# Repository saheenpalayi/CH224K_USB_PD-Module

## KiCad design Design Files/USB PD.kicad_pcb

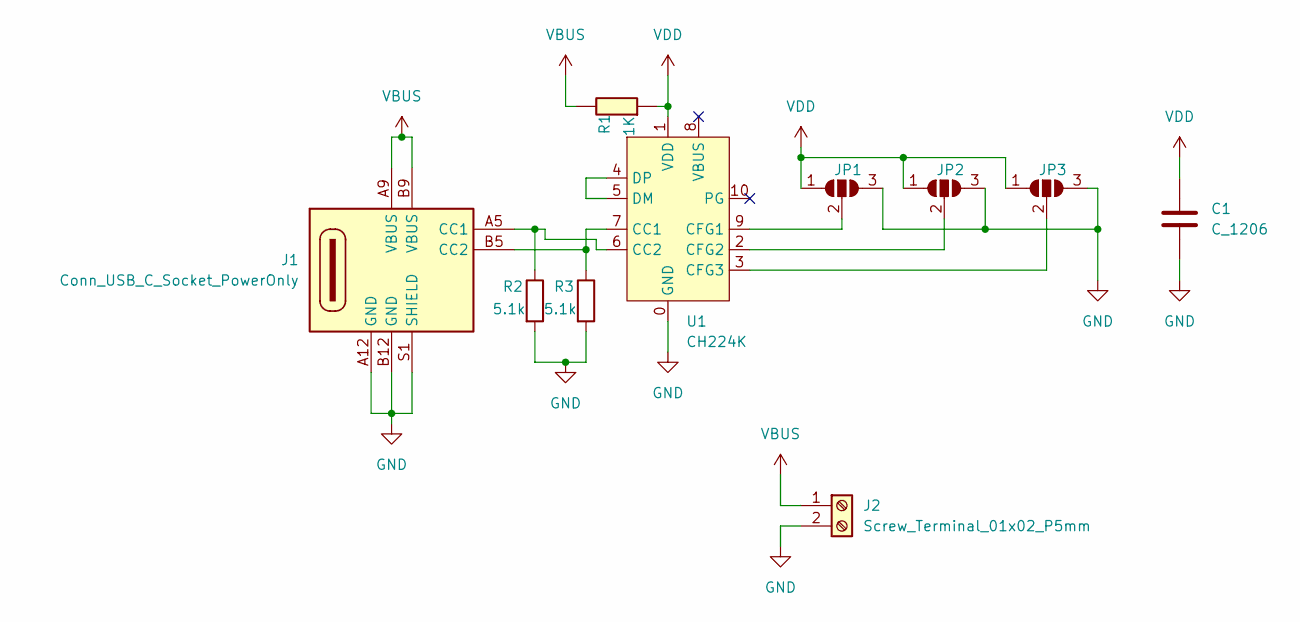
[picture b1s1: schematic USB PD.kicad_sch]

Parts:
C1: C_1206
J1: Conn_USB_C_Socket_PowerOnly; Conn_USB_C_Socket_GCT_USB4125-GF-A-0190
J2: Screw_Terminal_01x02_P5mm; TerminalBlock_OnShore_1x02_P5.00mm_Horizontal
JP1, JP2, JP3: SolderJumper_3_Open; SolderJumper-3_P1.3mm_Open_RoundedPad1.0x1.5mm
R1: 1K; R_1206
R2, R3: 5.1k; R_0805_2012Metric_Pad1.20x1.40mm_HandSolder
U1: CH224K; ESSOP-10_CH224K

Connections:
GND: C1.2, J1.A12 (GND), J1.B12 (GND), J1.S1 (SHIELD), J2.2, JP1.3 (B), JP2.3 (B), JP3.3 (B), R2.2, R3.2, U1.0 (GND)
unnamed: J1.A5 (CC1), R2.1, U1.6 (CC2)
unnamed: J1.B5 (CC2), R3.1, U1.7 (CC1)
unnamed: JP1.2 (C), U1.9 (CFG1)
unnamed: JP2.2 (C), U1.2 (CFG2)
unnamed: JP3.2 (C), U1.3 (CFG3)
unnamed: U1.4 (DP), U1.5 (DM)
VBUS: J1.A9 (VBUS), J1.B9 (VBUS), J2.1, R1.1
VDD: C1.1, JP1.1 (A), JP2.1 (A), JP3.1 (A), R1.2, U1.1 (VDD)

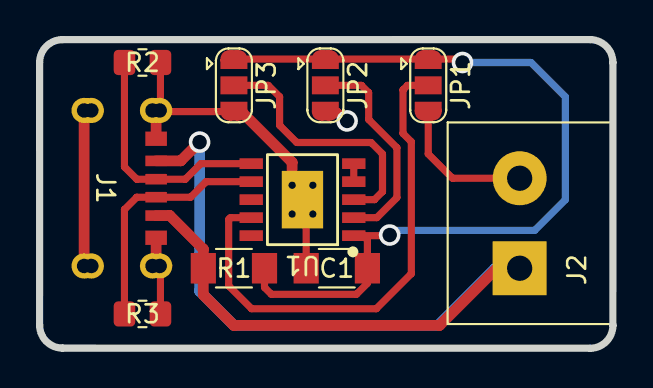
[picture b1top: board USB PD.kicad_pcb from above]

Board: 2 copper layers, 31.9 x 17.1 mm, 10 parts (0 on the bottom side), 9 nets.

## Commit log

2025-03-12 added files
